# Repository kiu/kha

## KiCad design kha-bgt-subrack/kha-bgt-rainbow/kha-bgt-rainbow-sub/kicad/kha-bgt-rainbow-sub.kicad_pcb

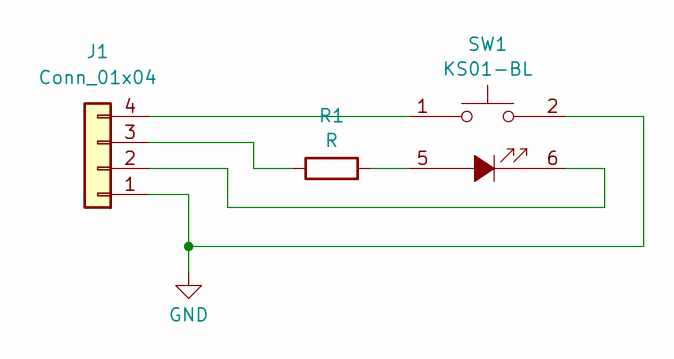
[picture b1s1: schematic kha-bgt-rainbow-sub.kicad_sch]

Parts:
J1: Conn_01x04; JST_PH_B4B-PH-K_1x04_P2.00mm_Vertical
R1: R; R_0805_2012Metric
SW1: KS01-BL

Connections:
GND: J1.1, SW1.2
unnamed: J1.2, SW1.6
unnamed: J1.3, R1.1
unnamed: J1.4, SW1.1
unnamed: R1.2, SW1.5

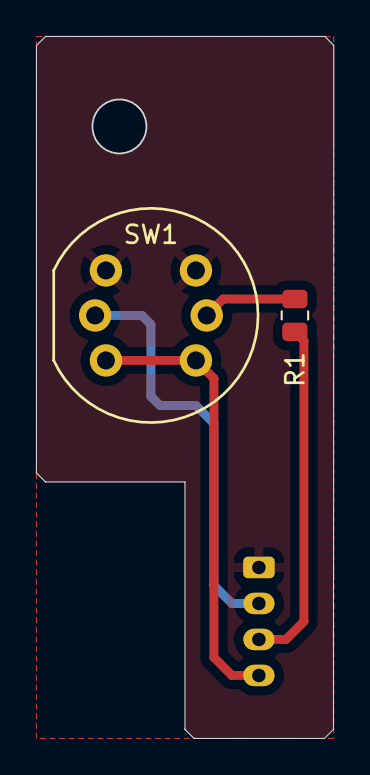
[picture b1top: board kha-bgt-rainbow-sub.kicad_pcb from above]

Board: 2 copper layers, 16.5 x 39.0 mm, 3 parts (1 on the bottom side), 5 nets.

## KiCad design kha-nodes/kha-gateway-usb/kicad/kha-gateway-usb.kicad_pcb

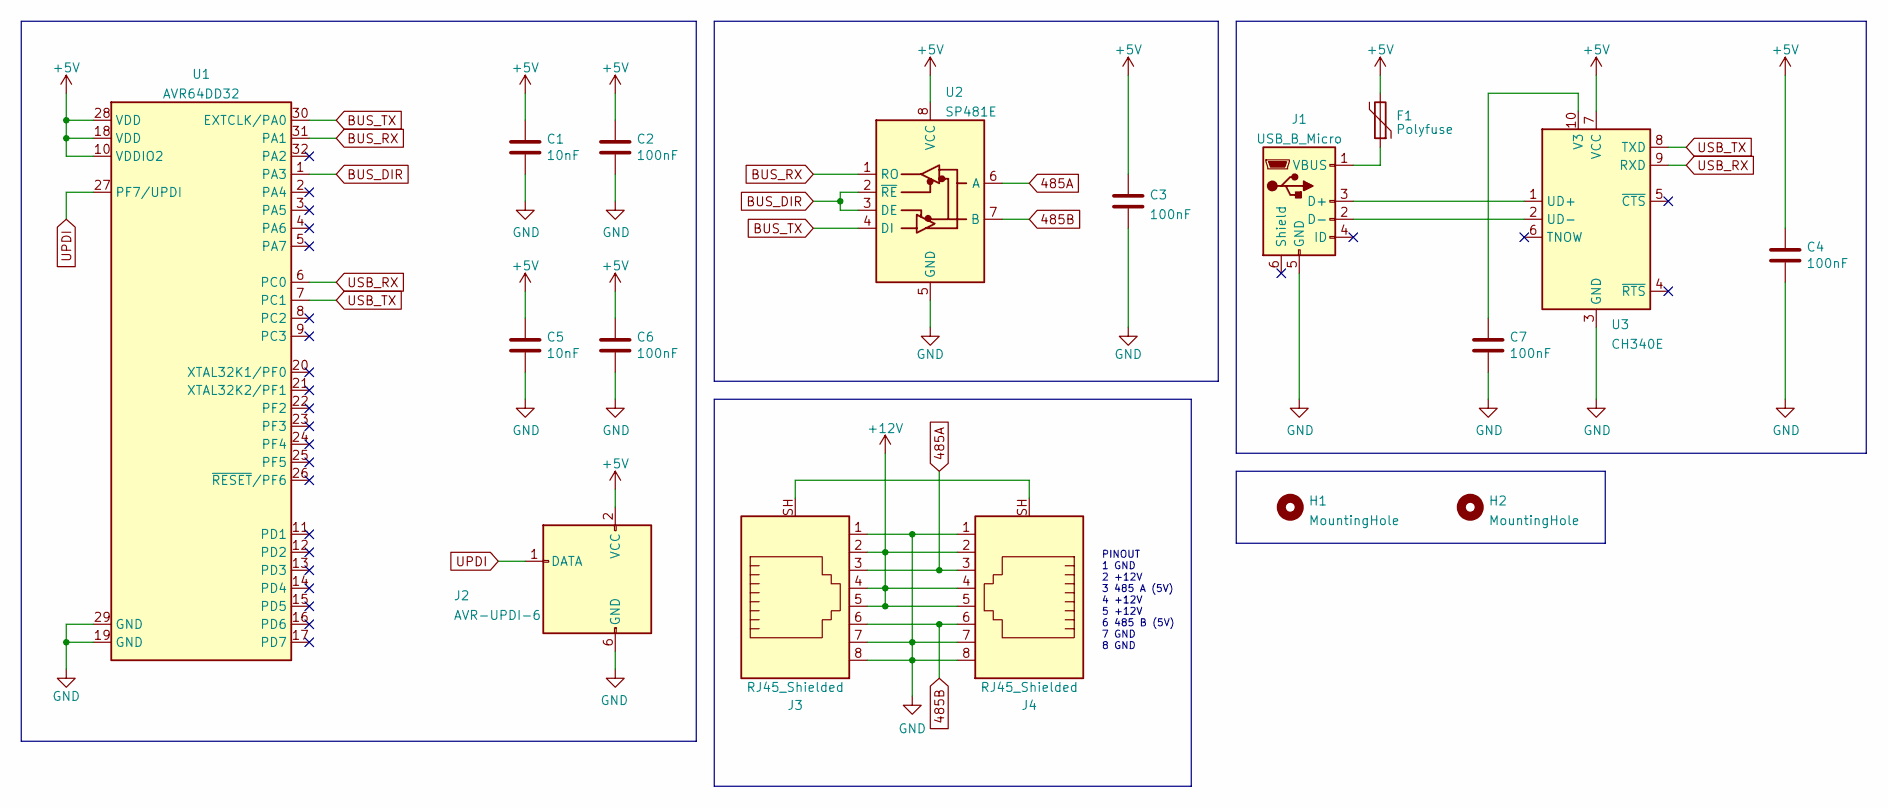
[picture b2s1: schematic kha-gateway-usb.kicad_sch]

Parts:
C1, C5: 10nF; C_0805_2012Metric
C2, C3, C4, C6, C7: 100nF; C_0805_2012Metric
F1: Polyfuse; Fuse_0805_2012Metric
H1, H2: MountingHole; MountingHole_3.7mm
J1: USB_B_Micro; GCT-USB3076-30-A
J2: AVR-UPDI-6; eAVR6-UPDI-F
J3, J4: RJ45_Shielded; GDLX-S-88K
U1: AVR64DD32; TQFP-32_7x7mm_P0.8mm
U2: SP481E; SOIC-8_3.9x4.9mm_P1.27mm
U3: CH340E; MSOP-10_3x3mm_P0.5mm

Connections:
485A: J3.3, J4.3, U2.6 (A)
485B: J3.6, J4.6, U2.7 (B)
+5V: C1.1, C2.1, C3.1, C4.1, C5.1, C6.1, F1.2, J2.2 (VCC), U1.10 (VDDIO2), U1.18 (VDD), U1.28 (VDD), U2.8 (VCC), U3.7 (VCC)
+12V: J3.2, J3.4, J3.5, J4.2, J4.4, J4.5
BUS_DIR: U1.1 (PA3), U2.2 (~RE), U2.3 (DE)
BUS_RX: U1.31 (PA1), U2.1 (RO)
BUS_TX: U1.30 (EXTCLK/PA0), U2.4 (DI)
GND: C1.2, C2.2, C3.2, C4.2, C5.2, C6.2, C7.2, J1.5 (GND), J2.6 (GND), J3.1, J3.7, J3.8, J4.1, J4.7, J4.8, U1.19 (GND), U1.29 (GND), U2.5 (GND), U3.3 (GND)
unnamed: J1.3 (D+), U3.1 (UD+)
unnamed: J1.2 (D-), U3.2 (UD-)
unnamed: F1.1, J1.1 (VBUS)
unnamed: J3.SH, J4.SH
unnamed: C7.1, U3.10 (V3)
UPDI: J2.1 (DATA), U1.27 (PF7/UPDI)
USB_RX: U1.6 (PC0), U3.9 (RXD)
USB_TX: U1.7 (PC1), U3.8 (TXD)

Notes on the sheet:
PINOUT 1 GND 2 +12V 3 485 A (5V) 4 +12V 5 +12V 6 485 B (5V) 7 GND 8 GND

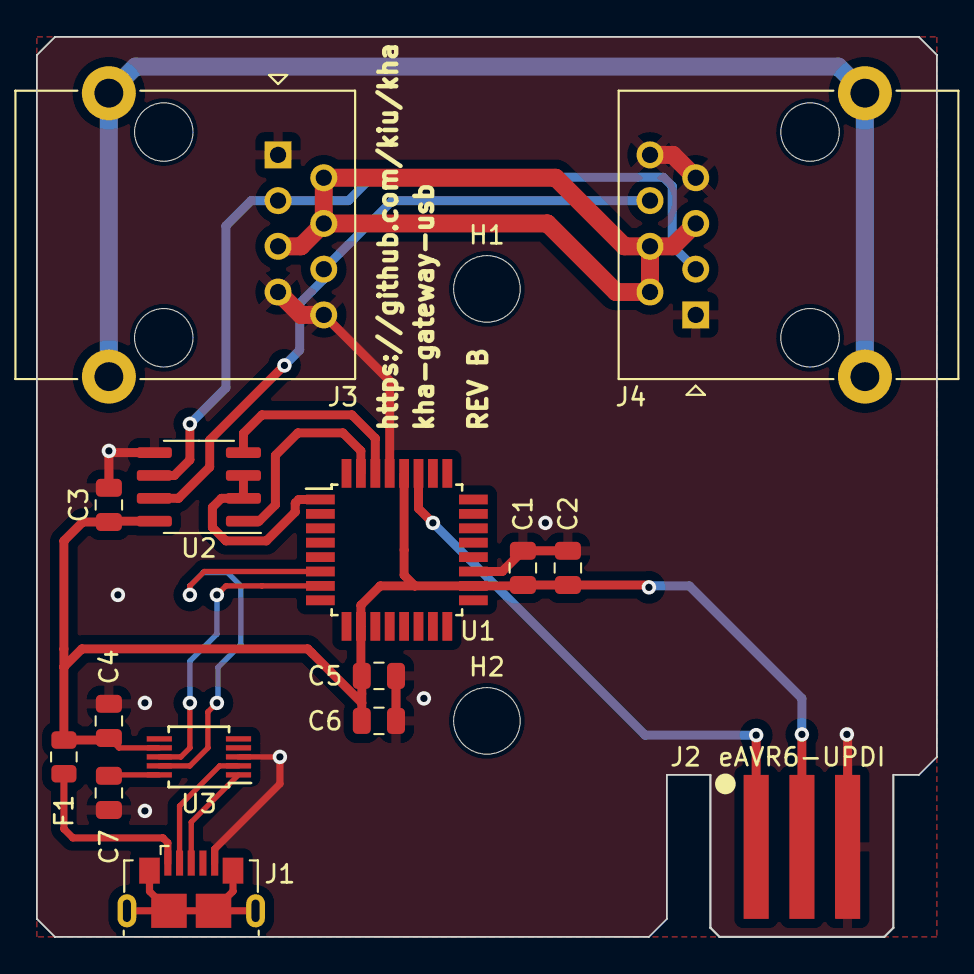
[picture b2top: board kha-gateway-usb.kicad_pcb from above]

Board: 2 copper layers, 50.0 x 50.0 mm, 17 parts (0 on the bottom side), 16 nets.

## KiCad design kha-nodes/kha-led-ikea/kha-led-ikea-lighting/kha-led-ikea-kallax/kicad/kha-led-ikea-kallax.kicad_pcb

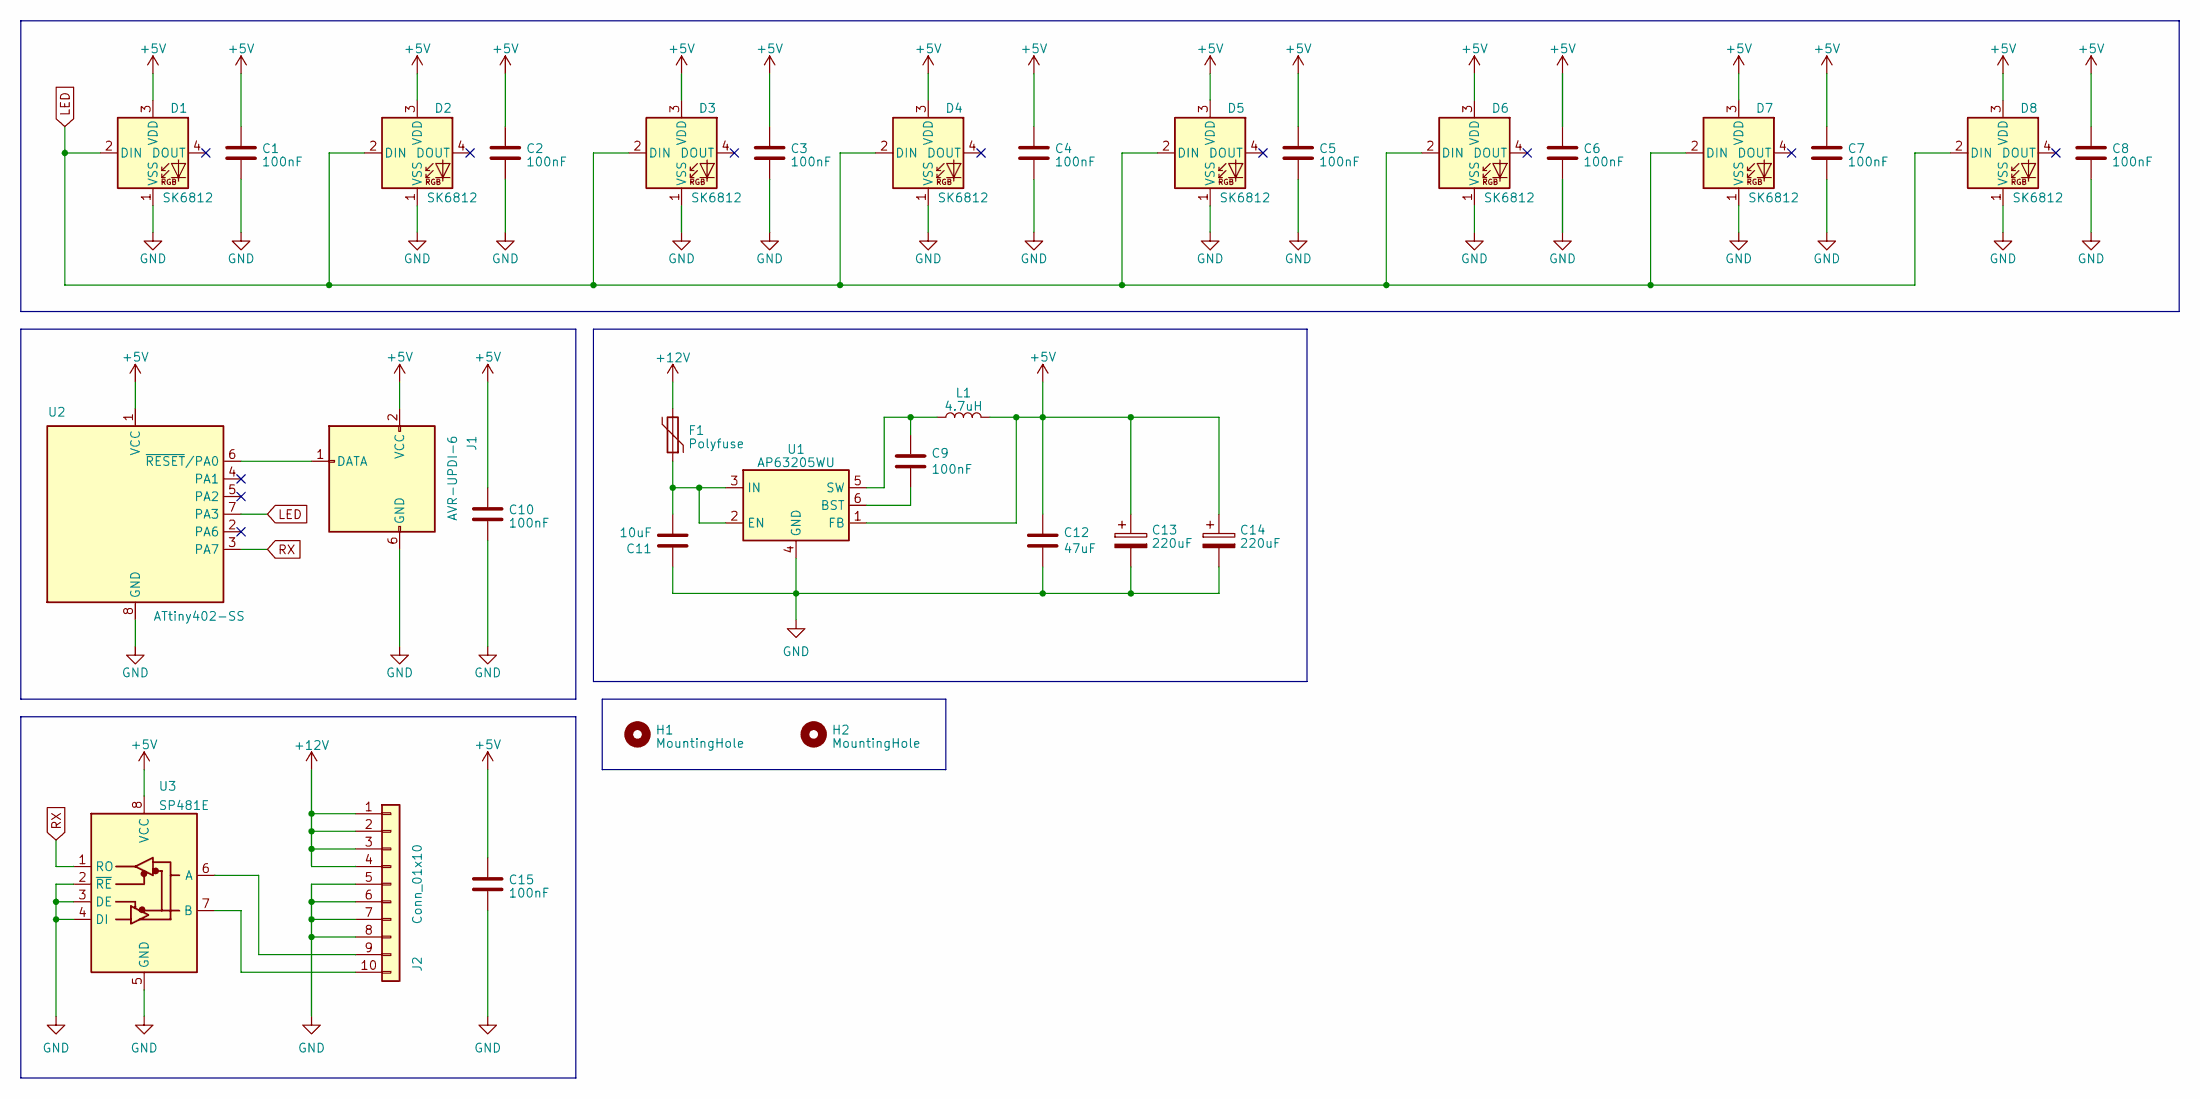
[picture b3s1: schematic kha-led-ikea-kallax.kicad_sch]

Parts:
C1, C2, C3, C4, C5, C6, C7, C8, C9, C10, C15: 100nF; C_0805_2012Metric
C11: 10uF; C_0805_2012Metric
C12: 47uF; C_1210_3225Metric
C13, C14: 220uF; CP_EIA-6032-28_Kemet-C
D1, D2, D3, D4, D5, D6, D7, D8: SK6812; LED_SK6812_PLCC4_5.0x5.0mm_P3.2mm
F1: Polyfuse; Fuse_0805_2012Metric
H1, H2: MountingHole; MountingHole_3.7mm
J1: AVR-UPDI-6; IDC-Header_2x03_P2.54mm_Vertical
J2: Conn_01x10; IDC-Header_2x05_P2.54mm_Vertical
L1: 4.7uH; L_1210_3225Metric
U1: AP63205WU; TSOT-23-6
U2: ATtiny402-SS; SOIC-8_3.9x4.9mm_P1.27mm
U3: SP481E; SOIC-8_3.9x4.9mm_P1.27mm

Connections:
+5V: C1.1, C2.1, C3.1, C4.1, C5.1, C6.1, C7.1, C8.1, C10.1, C12.1, C13.1, C14.1, C15.1, D1.3 (VDD), D2.3 (VDD), D3.3 (VDD), D4.3 (VDD), D5.3 (VDD), D6.3 (VDD), D7.3 (VDD), D8.3 (VDD), J1.2 (VCC), L1.2, U1.1 (FB), U2.1 (VCC), U3.8 (VCC)
+12V: F1.2, J2.1, J2.2, J2.3, J2.4
GND: C1.2, C2.2, C3.2, C4.2, C5.2, C6.2, C7.2, C8.2, C10.2, C11.1, C12.2, C13.2, C14.2, C15.2, D1.1 (VSS), D2.1 (VSS), D3.1 (VSS), D4.1 (VSS), D5.1 (VSS), D6.1 (VSS), D7.1 (VSS), D8.1 (VSS), J1.6 (GND), J2.5, J2.6, J2.7, J2.8, U1.4 (GND), U2.8 (GND), U3.2 (~RE), U3.3 (DE), U3.4 (DI), U3.5 (GND)
LED: D1.2 (DIN), D2.2 (DIN), D3.2 (DIN), D4.2 (DIN), D5.2 (DIN), D6.2 (DIN), D7.2 (DIN), D8.2 (DIN), U2.7 (PA3)
unnamed: J1.1 (DATA), U2.6 (~RESET/PA0)
unnamed: J2.9, U3.6 (A)
unnamed: J2.10, U3.7 (B)
unnamed: C9.2, U1.6 (BST)
unnamed: C11.2, F1.1, U1.2 (EN), U1.3 (IN)
unnamed: C9.1, L1.1, U1.5 (SW)
RX: U2.3 (PA7), U3.1 (RO)

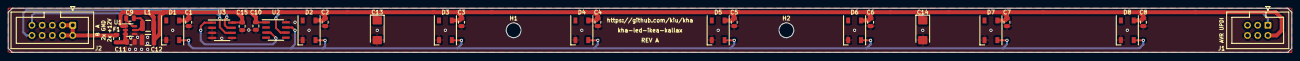
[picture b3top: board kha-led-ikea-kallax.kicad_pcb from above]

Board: 2 copper layers, 320.0 x 11.0 mm, 32 parts (0 on the bottom side), 11 nets.

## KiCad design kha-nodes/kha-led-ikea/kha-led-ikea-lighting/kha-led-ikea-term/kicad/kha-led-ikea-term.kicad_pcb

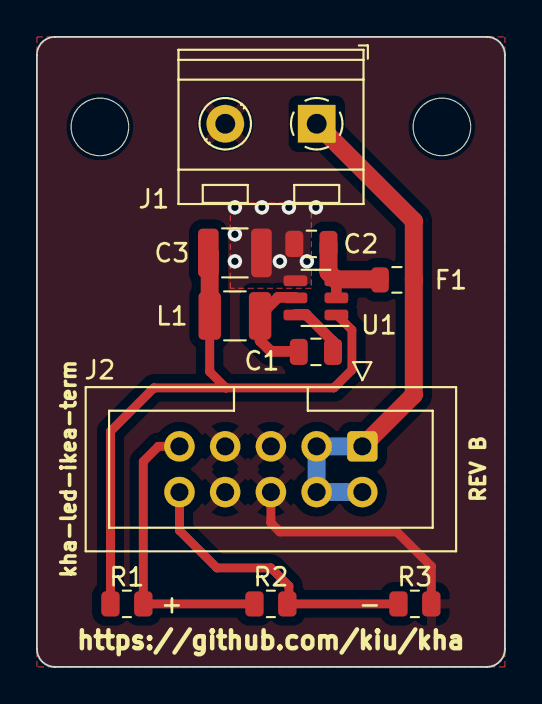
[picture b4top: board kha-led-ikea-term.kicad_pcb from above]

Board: 2 copper layers, 26.0 x 35.0 mm, 13 parts (0 on the bottom side), 8 nets.

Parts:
C1: 100nF; C_0805_2012Metric
C2: 10uF; C_0805_2012Metric
C3: 47uF; C_1210_3225Metric
F1: Polyfuse; Fuse_0805_2012Metric
H1, H2: MountingHole; MountingHole_3.2mm_M3
J1: Screw_Terminal_01x02; TerminalBlock_RND_205-00232_1x02_P5.08mm_Horizontal
J2: Conn_01x10; IDC-Header_2x05_P2.54mm_Vertical
L1: 4.7uH; L_1210_3225Metric
R1, R2, R3: R; R_0805_2012Metric
U1: AP63205WU; TSOT-23-6

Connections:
+5V: C3.1, L1.2, R1.1, U1.1 (FB)
+12V: F1.2, J1.1, J2.1, J2.2, J2.3, J2.4
GND: C2.1, C3.2, J1.2, J2.5, J2.6, J2.7, J2.8, R3.2, U1.4 (GND)
unnamed: J2.9, R1.2, R2.1
unnamed: J2.10, R2.2, R3.1
unnamed: C1.2, U1.6 (BST)
unnamed: C2.2, F1.1, U1.2 (EN), U1.3 (IN)
unnamed: C1.1, L1.1, U1.5 (SW)

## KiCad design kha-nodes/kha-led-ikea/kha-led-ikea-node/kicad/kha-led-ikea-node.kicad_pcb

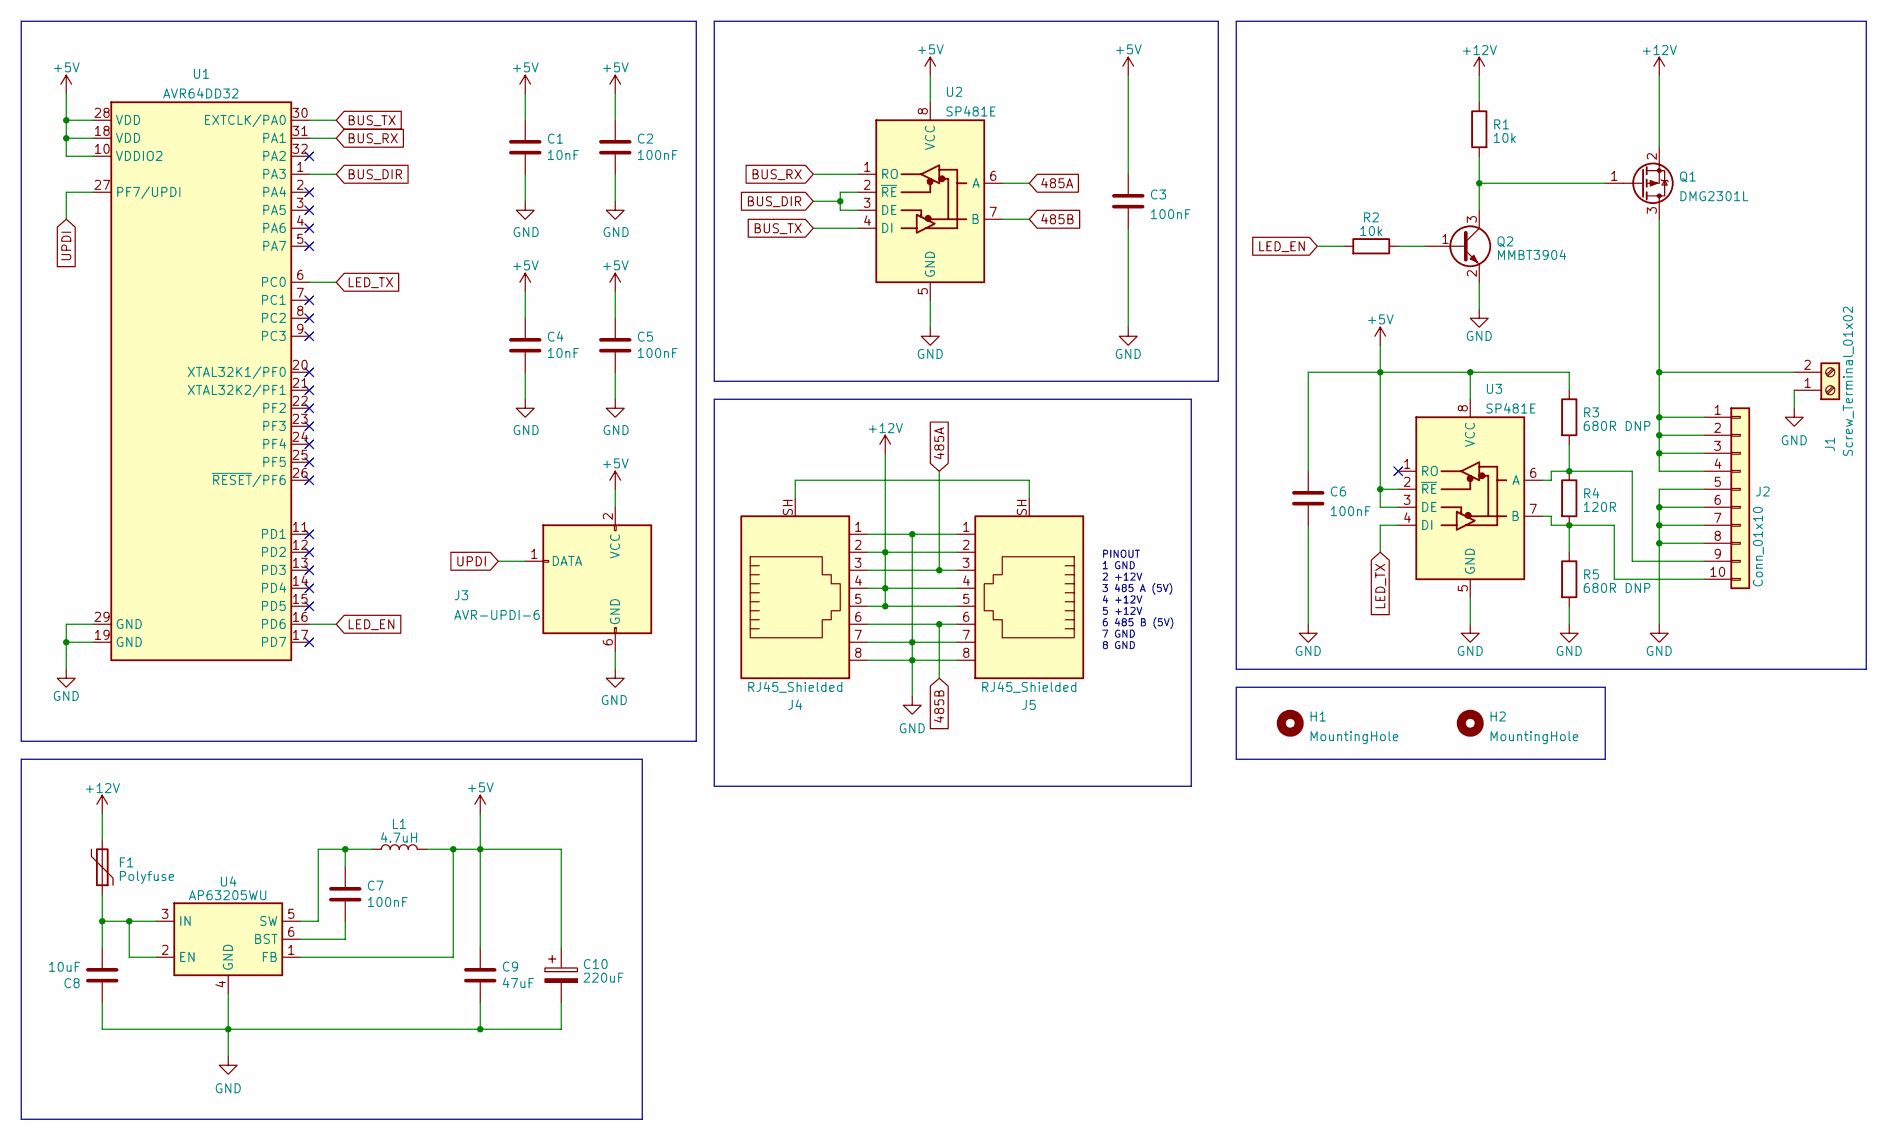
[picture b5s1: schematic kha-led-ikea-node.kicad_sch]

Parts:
C1, C4: 10nF; C_0805_2012Metric
C2, C3, C5, C6, C7: 100nF; C_0805_2012Metric
C8: 10uF; C_0805_2012Metric
C9: 47uF; C_1210_3225Metric
C10: 220uF; CP_EIA-6032-28_Kemet-C
F1: Polyfuse; Fuse_0805_2012Metric
H1, H2: MountingHole; MountingHole_3.2mm_M3_DIN965
J1: Screw_Terminal_01x02; TerminalBlock_bornier-2_P5.08mm
J2: Conn_01x10; IDC-Header_2x05_P2.54mm_Vertical
J3: AVR-UPDI-6; eAVR6-UPDI-F
J4, J5: RJ45_Shielded; GDLX-S-88K
L1: 4.7uH; L_1210_3225Metric
Q1: DMG2301L; SOT-23
Q2: MMBT3904; SOT-23
R1, R2: 10k; R_0805_2012Metric
R3, R5: 680R DNP; R_0805_2012Metric
R4: 120R; R_0805_2012Metric
U1: AVR64DD32; TQFP-32_7x7mm_P0.8mm
U2, U3: SP481E; SOIC-8_3.9x4.9mm_P1.27mm
U4: AP63205WU; TSOT-23-6

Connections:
485A: J4.3, J5.3, U2.6 (A)
485B: J4.6, J5.6, U2.7 (B)
+5V: C1.1, C2.1, C3.1, C4.1, C5.1, C6.1, C9.1, C10.1, J3.2 (VCC), L1.2, R3.1, U1.10 (VDDIO2), U1.18 (VDD), U1.28 (VDD), U2.8 (VCC), U3.2 (~RE), U3.3 (DE), U3.8 (VCC), U4.1 (FB)
+12V: F1.2, J4.2, J4.4, J4.5, J5.2, J5.4, J5.5, Q1.2 (S), R1.1
BUS_DIR: U1.1 (PA3), U2.2 (~RE), U2.3 (DE)
BUS_RX: U1.31 (PA1), U2.1 (RO)
BUS_TX: U1.30 (EXTCLK/PA0), U2.4 (DI)
GND: C1.2, C2.2, C3.2, C4.2, C5.2, C6.2, C8.1, C9.2, C10.2, J1.1, J2.5, J2.6, J2.7, J2.8, J3.6 (GND), J4.1, J4.7, J4.8, J5.1, J5.7, J5.8, Q2.2 (E), R5.2, U1.19 (GND), U1.29 (GND), U2.5 (GND), U3.5 (GND), U4.4 (GND)
LED_EN: R2.2, U1.16 (PD6)
LED_TX: U1.6 (PC0), U3.4 (DI)
unnamed: J1.2, J2.1, J2.2, J2.3, J2.4, Q1.3 (D)
unnamed: J2.9, R3.2, R4.1, U3.6 (A)
unnamed: J2.10, R4.2, R5.1, U3.7 (B)
unnamed: J4.SH, J5.SH
unnamed: Q1.1 (G), Q2.3 (C), R1.2
unnamed: Q2.1 (B), R2.1
unnamed: C7.2, U4.6 (BST)
unnamed: C8.2, F1.1, U4.2 (EN), U4.3 (IN)
unnamed: C7.1, L1.1, U4.5 (SW)
UPDI: J3.1 (DATA), U1.27 (PF7/UPDI)

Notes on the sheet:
PINOUT 1 GND 2 +12V 3 485 A (5V) 4 +12V 5 +12V 6 485 B (5V) 7 GND 8 GND

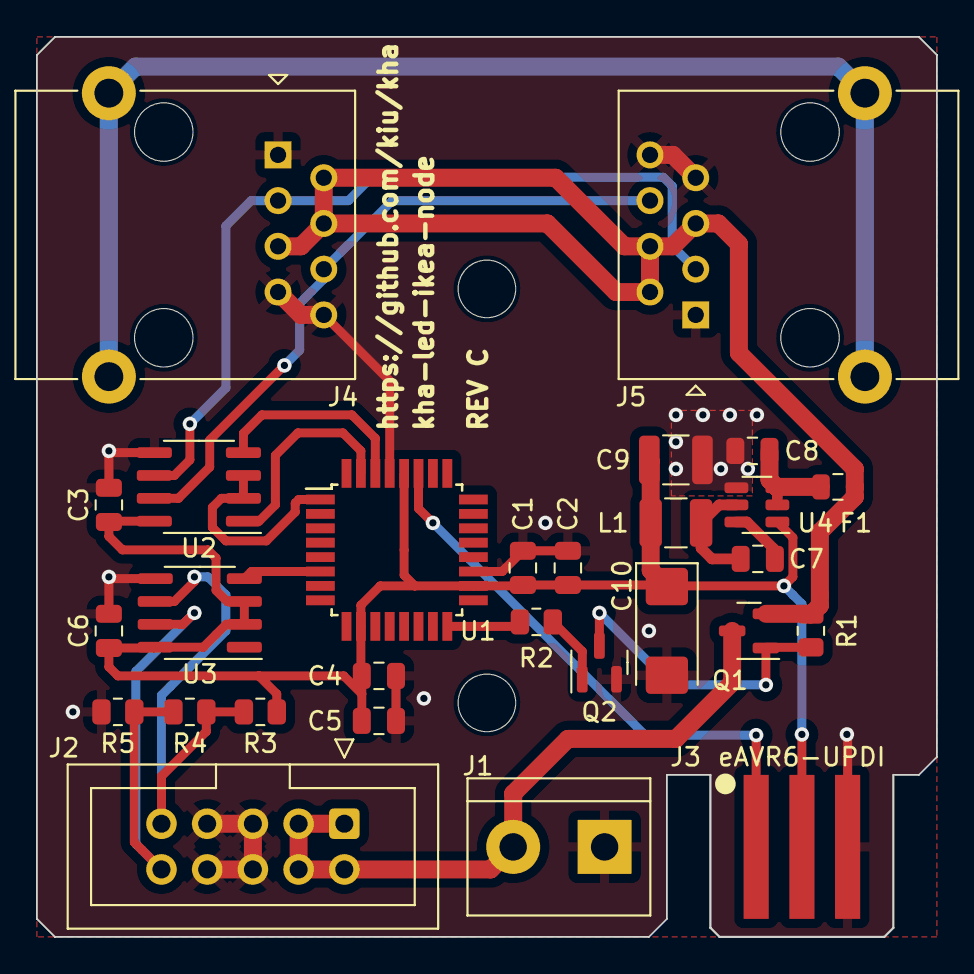
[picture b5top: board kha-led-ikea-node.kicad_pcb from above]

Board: 2 copper layers, 50.0 x 50.0 mm, 30 parts (0 on the bottom side), 20 nets.

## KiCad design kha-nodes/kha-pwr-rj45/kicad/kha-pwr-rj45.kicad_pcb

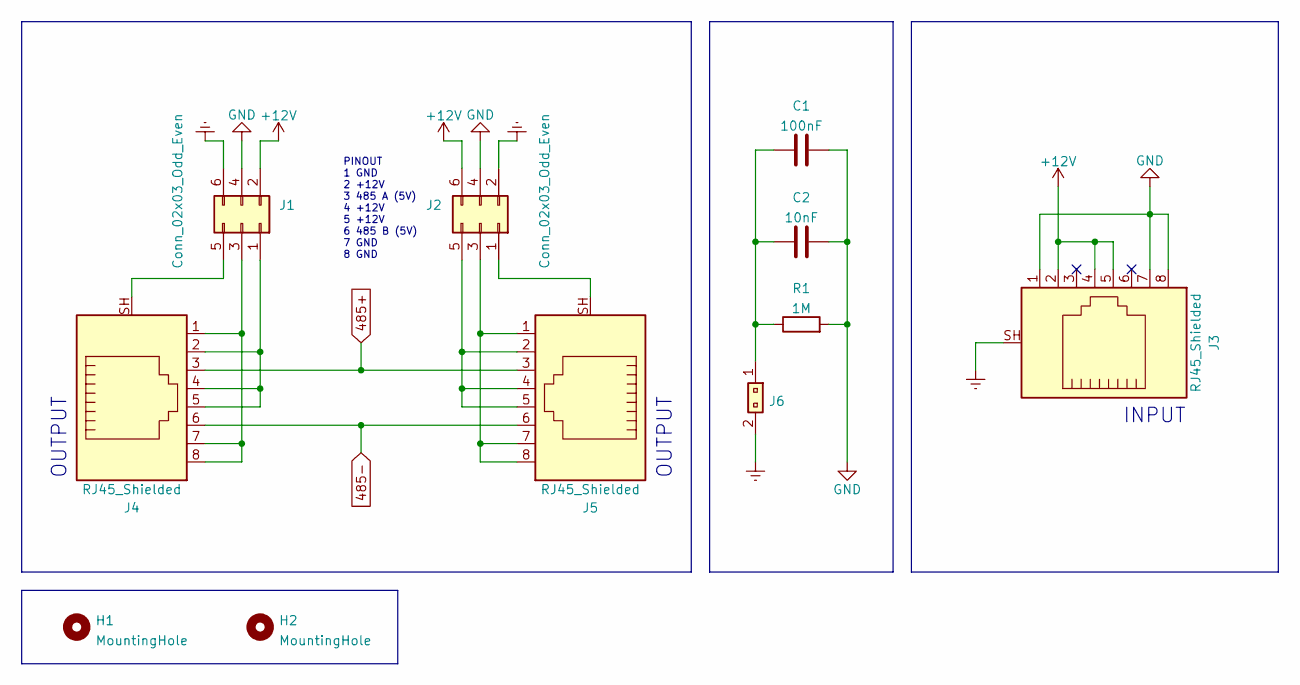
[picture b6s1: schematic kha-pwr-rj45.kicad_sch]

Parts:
C1: 100nF; C_0805_2012Metric
C2: 10nF; C_0805_2012Metric
H1, H2: MountingHole; MountingHole_3.2mm_M3
J1, J2: Conn_02x03_Odd_Even; PinHeader_2x03_P2.54mm_Vertical
J3, J4, J5: RJ45_Shielded; GDLX-S-88K
J6: 1x02_Jumper; PinHeader_1x02_P2.54mm_Vertical
R1: 1M; R_0805_2012Metric

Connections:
485+: J4.3, J5.3
485-: J4.6, J5.6
+12V: J1.2, J2.6, J3.2, J3.4, J3.5
Earth: J1.6, J2.2, J3.SH, J6.2
GND: C1.2, C2.2, J1.4, J2.4, J3.1, J3.7, J3.8, R1.2
unnamed: C1.1, C2.1, J6.1, R1.1
unnamed: J1.1, J4.2, J4.4, J4.5
unnamed: J1.3, J4.1, J4.7, J4.8
unnamed: J1.5, J4.SH
unnamed: J2.1, J5.SH
unnamed: J2.3, J5.1, J5.7, J5.8
unnamed: J2.5, J5.2, J5.4, J5.5

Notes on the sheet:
PINOUT 1 GND 2 +12V 3 485 A (5V) 4 +12V 5 +12V 6 485 B (5V) 7 GND 8 GND
INPUT
OUTPUT

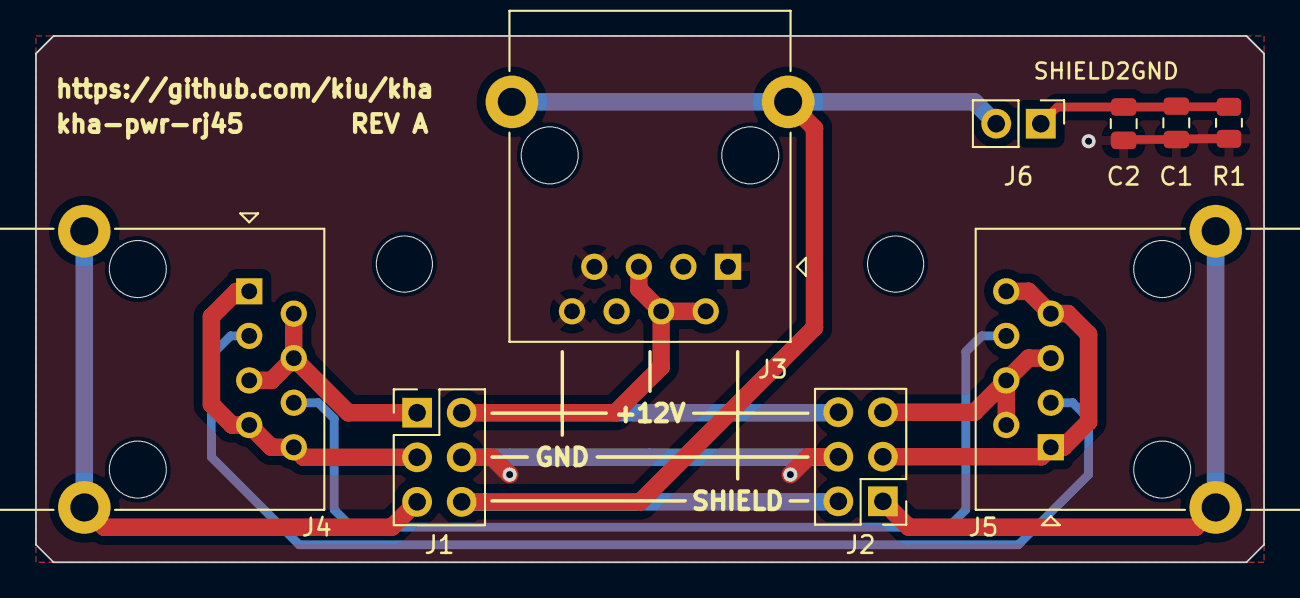
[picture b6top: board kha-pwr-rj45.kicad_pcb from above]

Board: 2 copper layers, 70.0 x 30.0 mm, 11 parts (0 on the bottom side), 12 nets.
